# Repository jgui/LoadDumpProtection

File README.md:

# LoadDumpProtection
Over-voltage protection circuit for sensitive device supplied by automotive-like 14V network.

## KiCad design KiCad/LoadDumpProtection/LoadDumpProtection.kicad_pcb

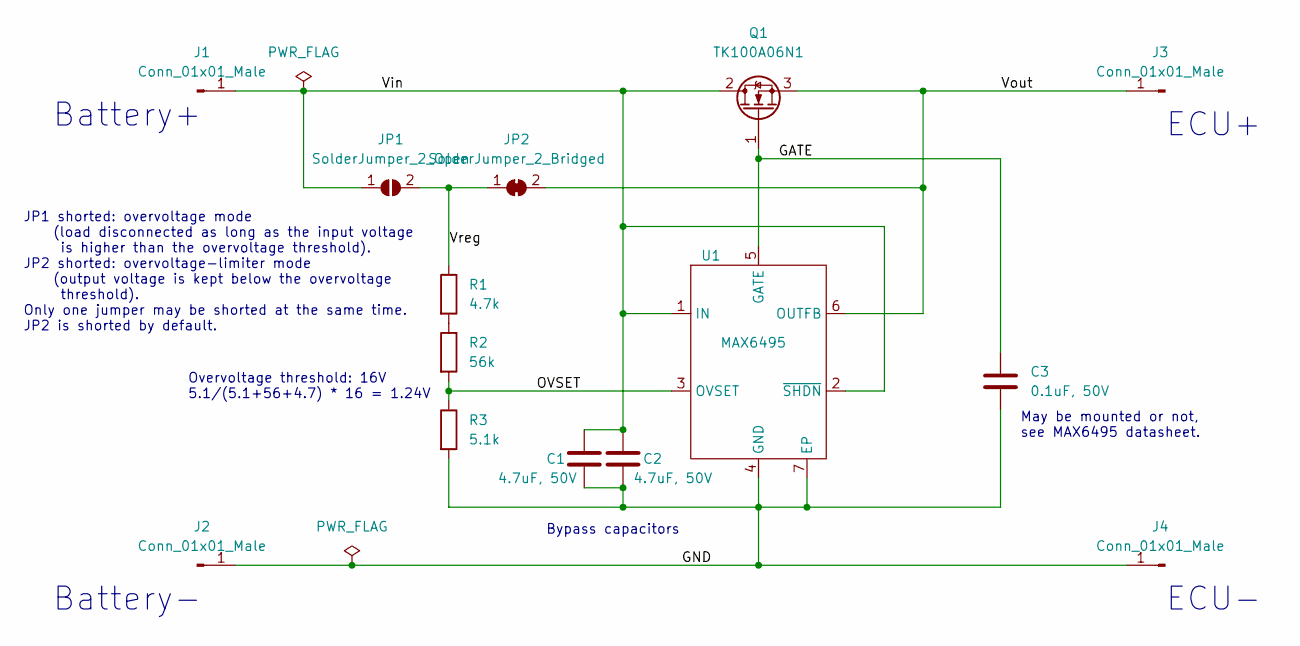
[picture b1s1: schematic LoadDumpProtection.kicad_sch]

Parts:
C1, C2: 4.7uF, 50V; C_1206_3216Metric_Pad1.33x1.80mm_HandSolder
C3: 0.1uF, 50V; C_1206_3216Metric_Pad1.33x1.80mm_HandSolder
J1, J2, J3, J4: Conn_01x01_Male; Pin_D1.3mm_L11.0mm
JP1: SolderJumper_2_Open; SolderJumper-2_P1.3mm_Open_Pad1.0x1.5mm
JP2: SolderJumper_2_Bridged; SolderJumper-2_P1.3mm_Bridged_Pad1.0x1.5mm
Q1: TK100A06N1; TO-220-3_Horizontal_TabDown
R1: 4.7k; R_0603_1608Metric_Pad0.98x0.95mm_HandSolder
R2: 56k; R_0603_1608Metric_Pad0.98x0.95mm_HandSolder
R3: 5.1k; R_0603_1608Metric_Pad0.98x0.95mm_HandSolder
U1: MAX6495; TDFN-6-1EP_3.0x3.0mm_P0.75mm_EP1.5x2.3mm

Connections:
/GATE: C3.1, Q1.1 (G), U1.5 (GATE)
/GND: C1.2, C2.2, C3.2, J2.1, J4.1, R3.2, U1.4 (GND), U1.7 (EP)
/OVSET: R2.2, R3.1, U1.3 (OVSET)
/Vin: C1.1, C2.1, J1.1, JP1.1 (A), Q1.2 (D), U1.1 (IN), U1.2 (~SHDN)
/Vout: J3.1, JP2.2 (B), Q1.3 (S), U1.6 (OUTFB)
/Vreg: JP1.2 (B), JP2.1 (A), R1.1
unnamed: R1.2, R2.1

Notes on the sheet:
May be mounted or not, see MAX6495 datasheet.
Battery+
Overvoltage threshold: 16V 5.1/(5.1+56+4.7) * 16 = 1.24V
JP1 shorted: overvoltage mode (load disconnected as long as the input voltage is higher than the overvoltage threshold). JP2 shorted: overvoltage-limiter mode (output voltage is kept below the overvoltage threshold). Only one jumper may be shorted at the same time. JP2 is shorted by default.
Bypass capacitors
ECU-
ECU+
Battery-

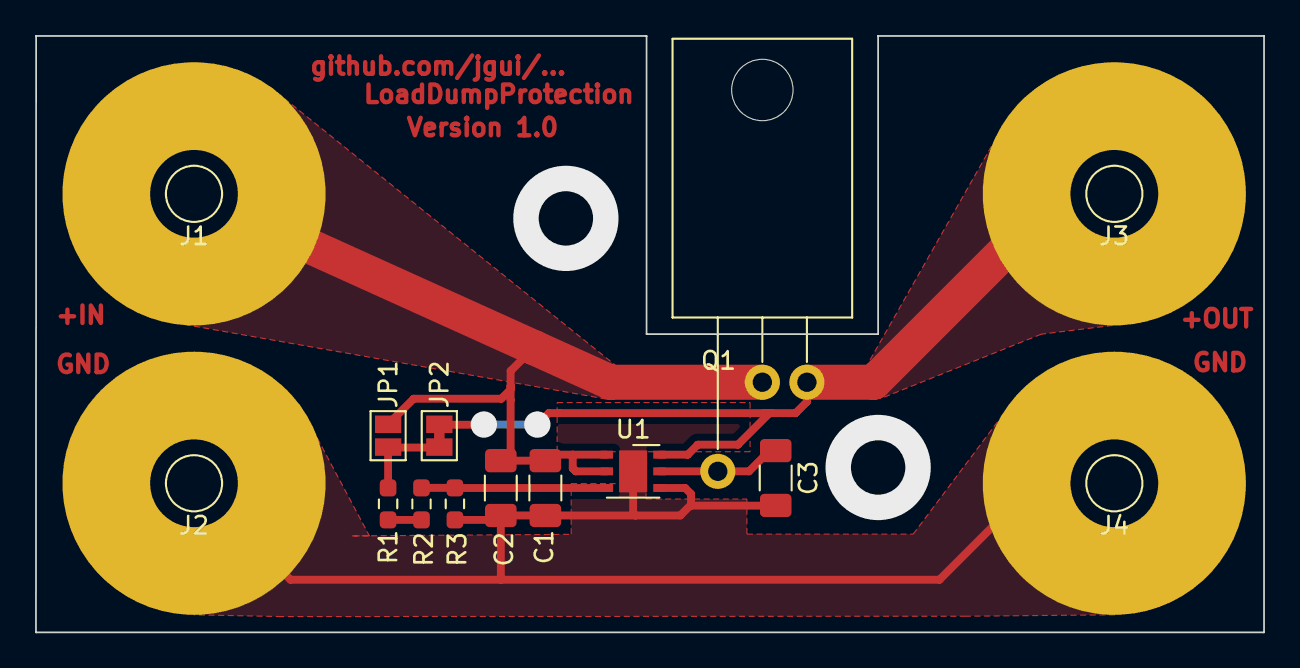
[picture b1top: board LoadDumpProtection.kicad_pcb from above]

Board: 2 copper layers, 70.0 x 34.0 mm, 14 parts (0 on the bottom side), 7 nets.

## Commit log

2022-07-05 KiCad PCB version 1.0
